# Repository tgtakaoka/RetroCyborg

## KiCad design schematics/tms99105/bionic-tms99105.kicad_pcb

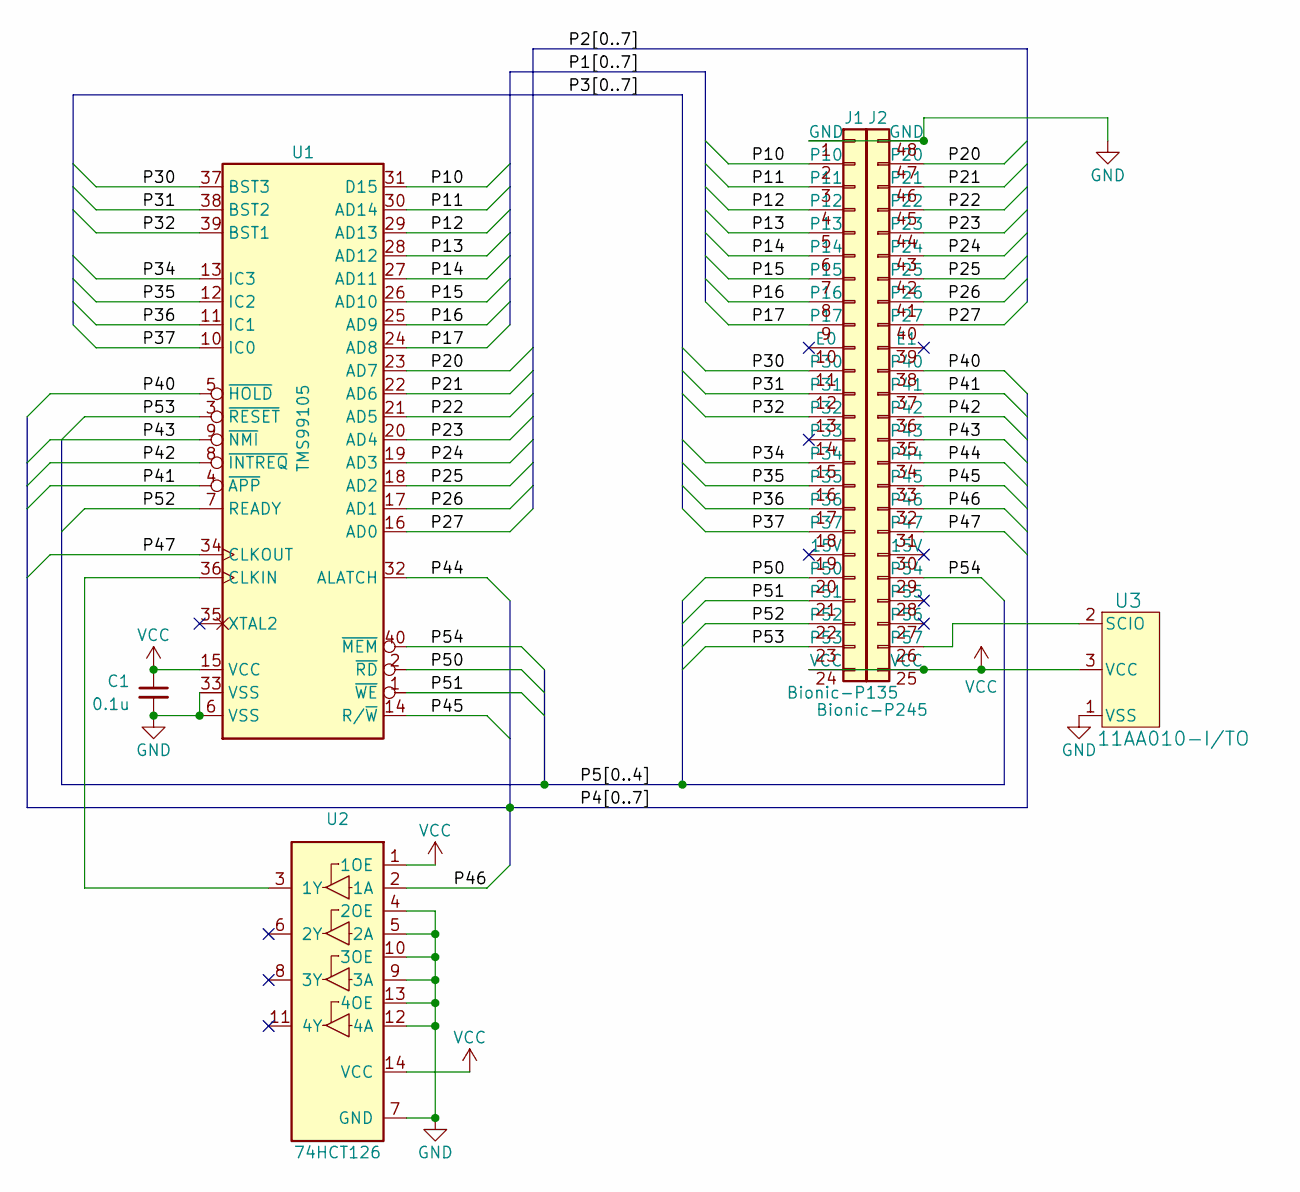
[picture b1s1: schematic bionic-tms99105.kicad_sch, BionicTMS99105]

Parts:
C1: 0.1u; C_Disc_D3.4mm_W2.1mm_P2.50mm
J1: Bionic-P135; Bionic-P135_Vertical
J2: Bionic-P245; Bionic-P245_Vertical
U1: TMS99105; DIP-40_W15.24mm
U2: 74HCT126; DIP-14_W7.62mm
U3: 11AA010-I/TO; TO-92_MC_MCH

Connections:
/P10: J1.2 (P10), U1.31 (D15)
/P11: J1.3 (P11), U1.30 (AD14)
/P12: J1.4 (P12), U1.29 (AD13)
/P13: J1.5 (P13), U1.28 (AD12)
/P14: J1.6 (P14), U1.27 (AD11)
/P15: J1.7 (P15), U1.26 (AD10)
/P16: J1.8 (P16), U1.25 (AD9)
/P17: J1.9 (P17), U1.24 (AD8)
/P20: J2.47 (P20), U1.23 (AD7)
/P21: J2.46 (P21), U1.22 (AD6)
/P22: J2.45 (P22), U1.21 (AD5)
/P23: J2.44 (P23), U1.20 (AD4)
/P24: J2.43 (P24), U1.19 (AD3)
/P25: J2.42 (P25), U1.18 (AD2)
/P26: J2.41 (P26), U1.17 (AD1)
/P27: J2.40 (P27), U1.16 (AD0)
/P30: J1.11 (P30), U1.37 (BST3)
/P31: J1.12 (P31), U1.38 (BST2)
/P32: J1.13 (P32), U1.39 (BST1)
/P34: J1.15 (P34), U1.13 (IC3)
/P35: J1.16 (P35), U1.12 (IC2)
/P36: J1.17 (P36), U1.11 (IC1)
/P37: J1.18 (P37), U1.10 (IC0)
/P40: J2.38 (P40), U1.5 (~HOLD)
/P41: J2.37 (P41), U1.4 (~APP)
/P42: J2.36 (P42), U1.8 (~INTREQ)
/P43: J2.35 (P43), U1.9 (~NMI)
/P44: J2.34 (P44), U1.32 (ALATCH)
/P45: J2.33 (P45), U1.14 (R/~W)
/P46: J2.32 (P46), U2.2 (1A)
/P47: J2.31 (P47), U1.34 (CLKOUT)
/P50: J1.20 (P50), U1.2 (~RD)
/P51: J1.21 (P51), U1.1 (~WE)
/P52: J1.22 (P52), U1.7 (READY)
/P53: J1.23 (P53), U1.3 (~RESET)
/P54: J2.29 (P54), U1.40 (~MEM)
GND: C1.2, J1.1 (GND), J2.48 (GND), U1.6 (VSS), U1.33 (VSS), U2.4 (2OE), U2.5 (2A), U2.7 (GND), U2.9 (3A), U2.10 (3OE), U2.12 (4A), U2.13 (4OE), U3.1 (VSS)
unnamed: J2.26 (P57), U3.2 (SCIO)
unnamed: U1.36 (CLKIN), U2.3 (1Y)
VCC: C1.1, J1.24 (VCC), J2.25 (VCC), U1.15 (VCC), U2.1 (1OE), U2.14 (VCC), U3.3 (VCC)

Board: 2 copper layers, 10 parts (0 on the bottom side), 40 nets, no tracks yet.

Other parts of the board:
MH1, MH2, MH3, MH4: MountingHole_3.2mm_M3

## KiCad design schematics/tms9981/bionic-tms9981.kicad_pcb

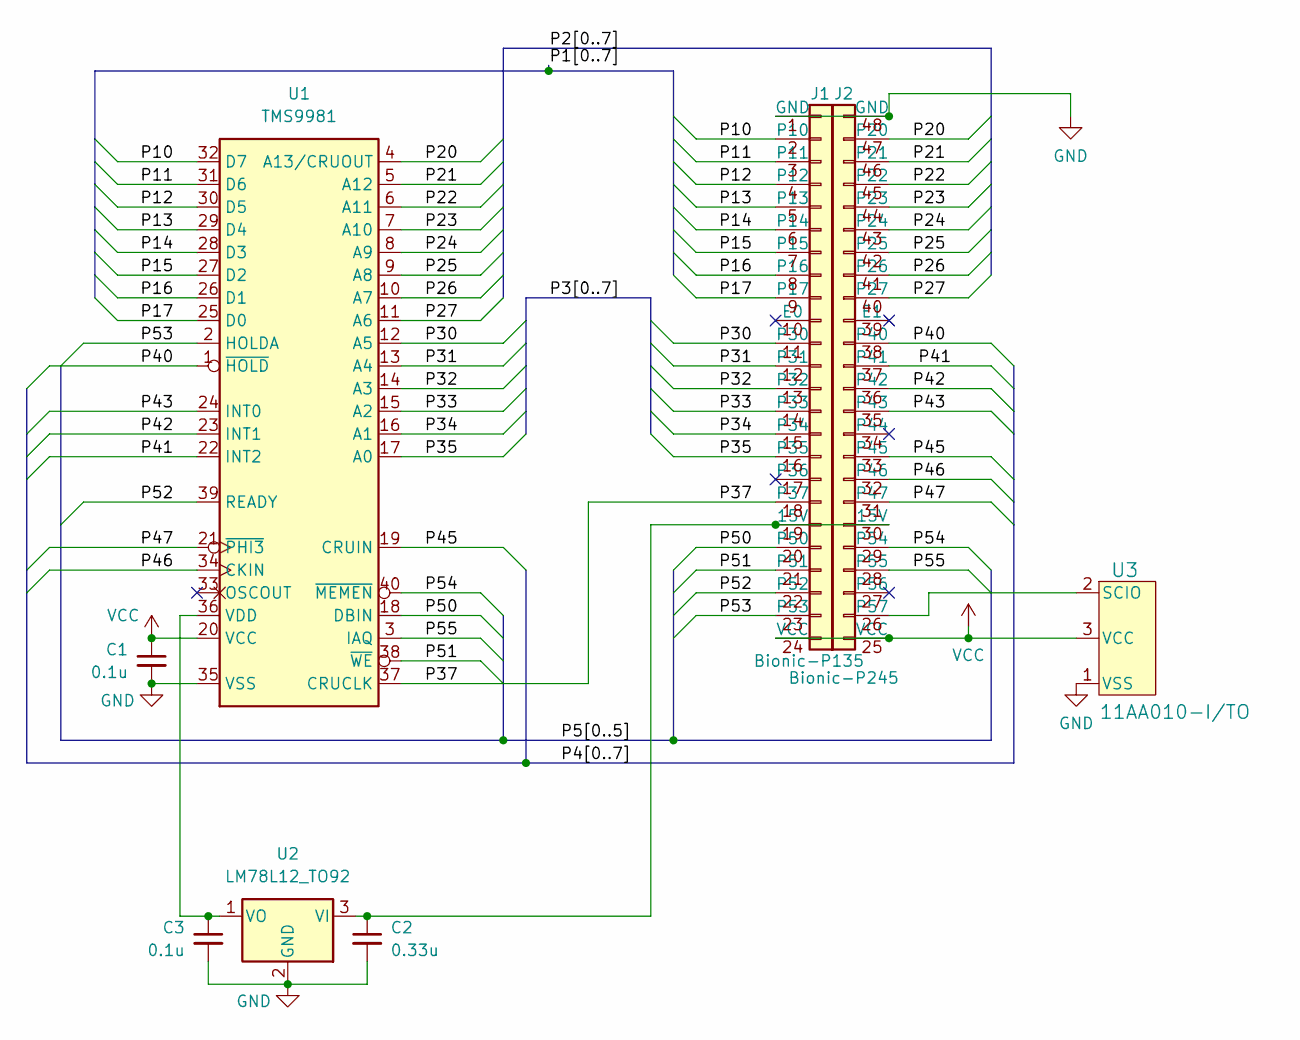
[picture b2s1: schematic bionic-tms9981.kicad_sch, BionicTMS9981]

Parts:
C1, C3: 0.1u; C_Disc_D3.4mm_W2.1mm_P2.50mm
C2: 0.33u; C_Disc_D3.4mm_W2.1mm_P2.50mm
J1: Bionic-P135; Bionic-P135_Vertical
J2: Bionic-P245; Bionic-P245_Vertical
U1: TMS9981; DIP-40_W15.24mm
U2: LM78L12_TO92; TO-92_Inline
U3: 11AA010-I/TO; TO-92_MC_MCH

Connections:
/P10: J1.2 (P10), U1.32 (D7); also elsewhere on the board
/P11: J1.3 (P11), U1.31 (D6); also elsewhere on the board
/P12: J1.4 (P12), U1.30 (D5); also elsewhere on the board
/P13: J1.5 (P13), U1.29 (D4); also elsewhere on the board
/P14: J1.6 (P14), U1.28 (D3); also elsewhere on the board
/P15: J1.7 (P15), U1.27 (D2); also elsewhere on the board
/P16: J1.8 (P16), U1.26 (D1); also elsewhere on the board
/P17: J1.9 (P17), U1.25 (D0); also elsewhere on the board
/P20: J1.47 (P20), J2.47 (P20), U1.4 (A13/CRUOUT)
/P21: J1.46 (P21), J2.46 (P21), U1.5 (A12)
/P22: J1.45 (P22), J2.45 (P22), U1.6 (A11)
/P23: J1.44 (P23), J2.44 (P23), U1.7 (A10)
/P24: J1.43 (P24), J2.43 (P24), U1.8 (A9)
/P25: J1.42 (P25), J2.42 (P25), U1.9 (A8)
/P26: J1.41 (P26), J2.41 (P26), U1.10 (A7)
/P27: J1.40 (P27), J2.40 (P27), U1.11 (A6)
/P30: J1.11 (P30), U1.12 (A5); also elsewhere on the board
/P31: J1.12 (P31), U1.13 (A4); also elsewhere on the board
/P32: J1.13 (P32), U1.14 (A3); also elsewhere on the board
/P33: J1.14 (P33), U1.15 (A2); also elsewhere on the board
/P34: J1.15 (P34), U1.16 (A1); also elsewhere on the board
/P35: J1.16 (P35), U1.17 (A0); also elsewhere on the board
/P37: J1.18 (P37), U1.37 (CRUCLK); also elsewhere on the board
/P40: J1.38 (P40), J2.38 (P40), U1.1 (~HOLD)
/P41: J1.37 (P41), J2.37 (P41), U1.22 (INT2)
/P42: J1.36 (P42), J2.36 (P42), U1.23 (INT1)
/P43: J1.35 (P43), J2.35 (P43), U1.24 (INT0)
/P45: J1.33 (P45), J2.33 (P45), U1.19 (CRUIN)
/P46: J1.32 (P46), J2.32 (P46), U1.34 (CKIN)
/P47: J1.31 (P47), J2.31 (P47), U1.21 (~PHI3)
/P50: J1.20 (P50), U1.18 (DBIN); also elsewhere on the board
/P51: J1.21 (P51), U1.38 (~WE); also elsewhere on the board
/P52: J1.22 (P52), U1.39 (READY); also elsewhere on the board
/P53: J1.23 (P53), U1.2 (HOLDA); also elsewhere on the board
/P54: J1.29 (P54), J2.29 (P54), U1.40 (~MEMEN)
/P55: J1.28 (P55), J2.28 (P55), U1.3 (IAQ)
GND: C1.2, C2.2, C3.2, J1.1 (GND), J1.48 (GND), J2.48 (GND), U1.35 (VSS), U2.2 (GND), U3.1 (VSS); also elsewhere on the board
unnamed: J2.26 (P57), U3.2 (SCIO)
unnamed: C3.1, U1.36 (VDD), U2.1 (VO)
VCC: C1.1, J1.24 (VCC), J1.25 (VCC), J2.25 (VCC), U1.20 (VCC), U3.3 (VCC); also elsewhere on the board

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
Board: 2 copper layers, 13 parts (0 on the bottom side), 42 nets, no tracks yet.

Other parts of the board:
J1#2: Bionic-P135; Bionic-P135_Vertical
MH1, MH2, MH3, MH4: MountingHole_3.2mm_M3

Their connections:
/P10: J1#2.2 (P10); also elsewhere on the board
/P11: J1#2.3 (P11); also elsewhere on the board
/P12: J1#2.4 (P12); also elsewhere on the board
/P13: J1#2.5 (P13); also elsewhere on the board
/P14: J1#2.6 (P14); also elsewhere on the board
/P15: J1#2.7 (P15); also elsewhere on the board
/P16: J1#2.8 (P16); also elsewhere on the board
/P17: J1#2.9 (P17); also elsewhere on the board
/P30: J1#2.11 (P30); also elsewhere on the board
/P31: J1#2.12 (P31); also elsewhere on the board
/P32: J1#2.13 (P32); also elsewhere on the board
/P33: J1#2.14 (P33); also elsewhere on the board
/P34: J1#2.15 (P34); also elsewhere on the board
/P35: J1#2.16 (P35); also elsewhere on the board
/P37: J1#2.18 (P37); also elsewhere on the board
/P50: J1#2.20 (P50); also elsewhere on the board
/P51: J1#2.21 (P51); also elsewhere on the board
/P52: J1#2.22 (P52); also elsewhere on the board
/P53: J1#2.23 (P53); also elsewhere on the board
GND: J1#2.1 (GND); also elsewhere on the board
VCC: J1#2.24 (VCC); also elsewhere on the board

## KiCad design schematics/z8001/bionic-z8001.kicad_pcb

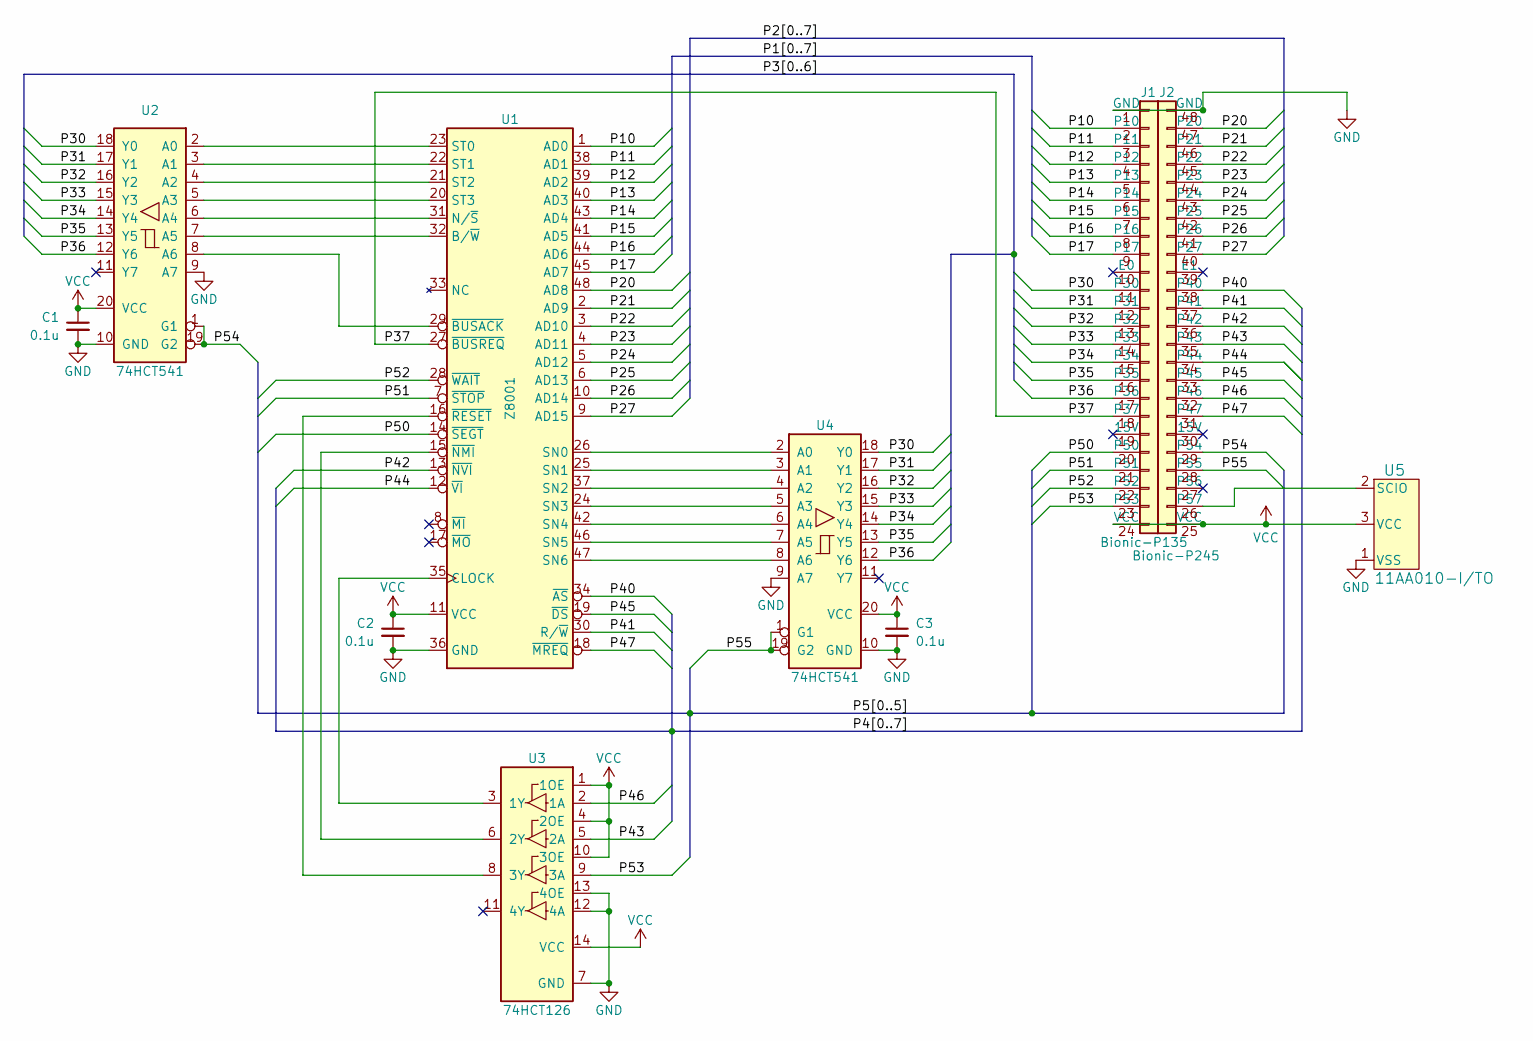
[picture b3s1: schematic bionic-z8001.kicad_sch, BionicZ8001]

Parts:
C1, C2, C3: 0.1u; C_Disc_D3.4mm_W2.1mm_P2.50mm
J1: Bionic-P135; Bionic-P135_Vertical
J2: Bionic-P245; Bionic-P245_Vertical
U1: Z8001; DIP-48_W15.24mm
U2, U4: 74HCT541; DIP-20_W7.62mm
U3: 74HCT126; DIP-14_W7.62mm
U5: 11AA010-I/TO; TO-92_MC_MCH

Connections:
/P10: J1.2 (P10), U1.1 (AD0)
/P11: J1.3 (P11), U1.38 (AD1)
/P12: J1.4 (P12), U1.39 (AD2)
/P13: J1.5 (P13), U1.40 (AD3)
/P14: J1.6 (P14), U1.43 (AD4)
/P15: J1.7 (P15), U1.41 (AD5)
/P16: J1.8 (P16), U1.44 (AD6)
/P17: J1.9 (P17), U1.45 (AD7)
/P20: J2.47 (P20), U1.48 (AD8)
/P21: J2.46 (P21), U1.2 (AD9)
/P22: J2.45 (P22), U1.3 (AD10)
/P23: J2.44 (P23), U1.4 (AD11)
/P24: J2.43 (P24), U1.5 (AD12)
/P25: J2.42 (P25), U1.6 (AD13)
/P26: J2.41 (P26), U1.10 (AD14)
/P27: J2.40 (P27), U1.9 (AD15)
/P30: J1.11 (P30), U2.18 (Y0), U4.18 (Y0)
/P31: J1.12 (P31), U2.17 (Y1), U4.17 (Y1)
/P32: J1.13 (P32), U2.16 (Y2), U4.16 (Y2)
/P33: J1.14 (P33), U2.15 (Y3), U4.15 (Y3)
/P34: J1.15 (P34), U2.14 (Y4), U4.14 (Y4)
/P35: J1.16 (P35), U2.13 (Y5), U4.13 (Y5)
/P36: J1.17 (P36), U2.12 (Y6), U4.12 (Y6)
/P37: J1.18 (P37), U1.27 (~BUSREQ)
/P40: J2.38 (P40), U1.34 (~AS)
/P41: J2.37 (P41), U1.30 (R/~W)
/P42: J2.36 (P42), U1.13 (~NVI)
/P43: J2.35 (P43), U3.5 (2A)
/P44: J2.34 (P44), U1.12 (~VI)
/P45: J2.33 (P45), U1.19 (~DS)
/P46: J2.32 (P46), U3.2 (1A)
/P47: J2.31 (P47), U1.18 (~MREQ)
/P50: J1.20 (P50), U1.14 (~SEGT)
/P51: J1.21 (P51), U1.7 (~STOP)
/P52: J1.22 (P52), U1.28 (~WAIT)
/P53: J1.23 (P53), U3.9 (3A)
/P54: J2.29 (P54), U2.1 (G1), U2.19 (G2)
/P55: J2.28 (P55), U4.1 (G1), U4.19 (G2)
GND: C1.2, C2.2, C3.2, J1.1 (GND), J2.48 (GND), U1.36 (GND), U2.9 (A7), U2.10 (GND), U3.7 (GND), U3.12 (4A), U3.13 (4OE), U4.9 (A7), U4.10 (GND), U5.1 (VSS)
unnamed: J2.26 (P57), U5.2 (SCIO)
unnamed: U1.32 (B/~W), U2.7 (A5)
unnamed: U1.35 (CLOCK), U3.3 (1Y)
unnamed: U1.31 (N/~S), U2.6 (A4)
unnamed: U1.26 (SN0), U4.2 (A0)
unnamed: U1.25 (SN1), U4.3 (A1)
unnamed: U1.37 (SN2), U4.4 (A2)
unnamed: U1.24 (SN3), U4.5 (A3)
unnamed: U1.42 (SN4), U4.6 (A4)
unnamed: U1.46 (SN5), U4.7 (A5)
unnamed: U1.47 (SN6), U4.8 (A6)
unnamed: U1.23 (ST0), U2.2 (A0)
unnamed: U1.22 (ST1), U2.3 (A1)
unnamed: U1.21 (ST2), U2.4 (A2)
unnamed: U1.20 (ST3), U2.5 (A3)
unnamed: U1.29 (~BUSACK), U2.8 (A6)
unnamed: U1.15 (~NMI), U3.6 (2Y)
unnamed: U1.16 (~RESET), U3.8 (3Y)
VCC: C1.1, C2.1, C3.1, J1.24 (VCC), J2.25 (VCC), U1.11 (VCC), U2.20 (VCC), U3.1 (1OE), U3.4 (2OE), U3.10 (3OE), U3.14 (VCC), U4.20 (VCC), U5.3 (VCC)

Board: 2 copper layers, 14 parts (0 on the bottom side), 58 nets, no tracks yet.

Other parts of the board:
MH1, MH2, MH3, MH4: MountingHole_3.2mm_M3
